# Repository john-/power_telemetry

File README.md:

Device that converts 12v to 5v, measures power/other things, and controls 4-wire fans.

# DESIGN NOTES

The 3rd 5V converter powers ICs and is a backup

**Power Sensing**

_Calibration_

V bus max   = 16V
V shunt max = 320㎷ (PGA = ÷8)
R shunt     = 0.1Ω

I max possible = V shunt max ÷ R shunt = 3.2A

I max expected = 3A (this needs to be revisited with better understanding of what it represents)

_Serial Bus Address_

Ground A0 and A1 to get adress of 1000000.

I²C bus pull-up resistors of 4.7KΩ was not calculated.  It was from arbitrary site.   The INA219 datasheet references 3.3KΩ.

_Optional Filter_

As filtering may not be needed initial implementation will be 0Ω resistors (R6/7) and capacitor (C3) unpopulated.

_Bypass Capacitors_

Values are taken from datasheet.  Ceramic type chosen from arbitrary page.

Design mistakes:

- I did not include any temp sensors! Now when I read the data sheet for the ADT7470 it makes it clear it is can't do standalone temperature measuring. I previously assumed it had one built-in temperature sensor. Anyway, I will use manual control of the ADT7470 based on temperature of SBCs (there will be 2 Odroid C2s in the case). I may add an external temperature sensor for the temperature sensor. Previously I have used 1 wire sensor. I need to confirm I can use 1 wire and I2C at same time on C2.
- The circuit puts out 5V I2C and the C2 max input voltage 3.3V. I happen to have a level shifter to get things working. I should have had the circuit output 3.3V I2C.
- I am pretty sure I should have included GND with the SDA/SCL lines. Since I had to use the level shifter I wound up pulling in 5V/GND from elsewhere in the circuit.

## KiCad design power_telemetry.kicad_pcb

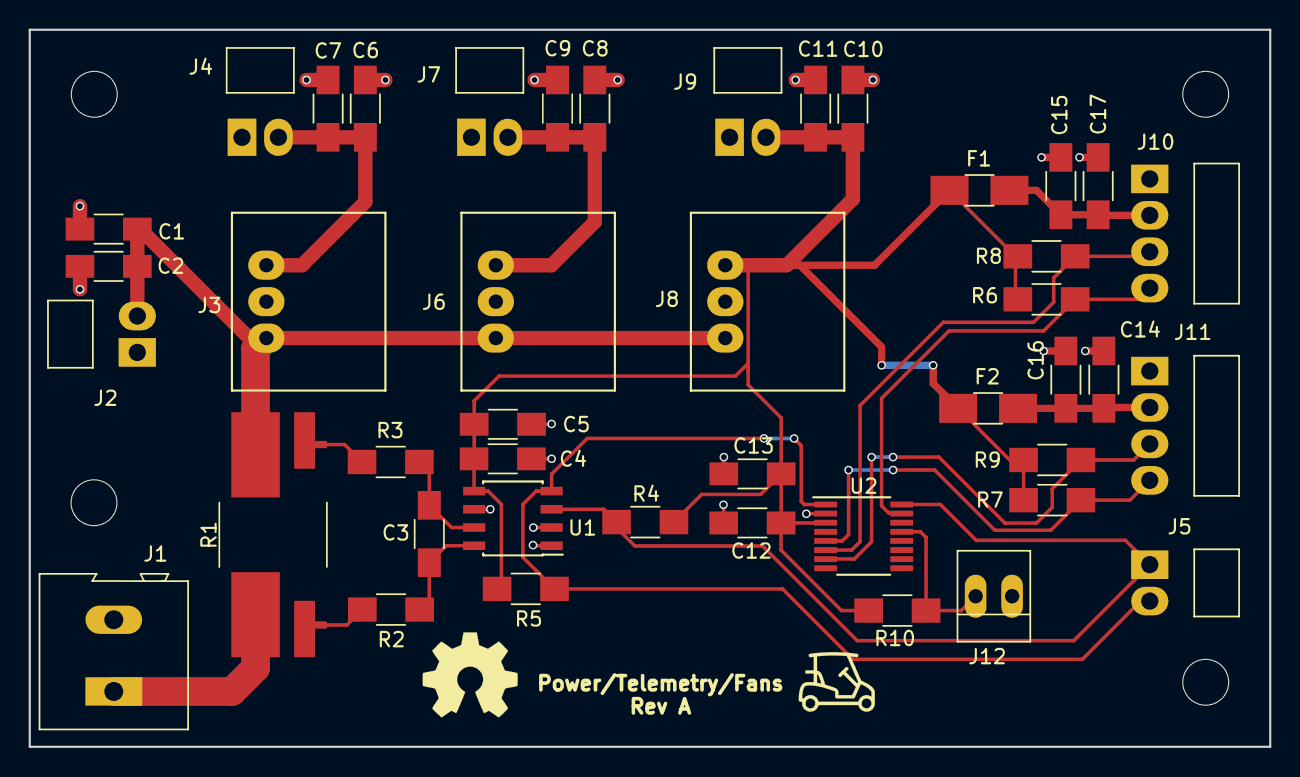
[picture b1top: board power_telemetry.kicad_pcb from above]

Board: 2 copper layers, 86.5 x 50.0 mm, 43 parts (0 on the bottom side), 17 nets.

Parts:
C1, C4, C6, C8, C10, C13, C15, C16: 10uF; C_1206_HandSoldering
C2, C5, C7, C9, C11, C12, C14, C17: 0.1uF; C_1206_HandSoldering
C3: C; C_1206_HandSoldering
F1, F2: 0.5A PTC; Fuse_SMD1206_HandSoldering
J1: Screw_Terminal_1x02; TER-202
J2, J4, J5, J7, J9: CONN_01X02; Molex_KK-171857-02x2.54mm_Right
J3, J6, J8: CONN_01X03; DCDC-Conv_Murata_OKI-78SR-E
J10, J11: CONN_01X04; Molex_KK-171857-04x2.54mm_Right
J12: GS2; PINHEAD1-2
R1: 100 mOhms; R_4527_Kelvin2_HandSoldering
R2, R3: 0k; R_1206_HandSoldering
R4, R5: 4.7k; R_1206_HandSoldering
R6, R7, R8, R9, R10: 10k; R_1206_HandSoldering
U1: TI_INA219_SOIC; SOIC-8_3.9x4.9mm_Pitch1.27mm
U2: AD_ADT7470_QSOP; QSOP-16_3.9x4.9mm_Pitch0.635mm

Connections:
+12V: C1.2, C2.2, J2.2, J3.1, J6.1, J8.1, R1.2, R3.1
/SCL: J5.2, R5.2, U1.4, U2.1
/SDA: J5.1, R4.2, U1.3, U2.16
/VCCA: C8.2, C9.1, J6.3, J7.2
/VCCB: C6.2, C7.2, J3.3, J4.2
GND: C1.1, C2.1, C4.2, C5.2, C6.1, C7.1, C8.1, C9.2, C10.1, C11.2, C12.2, C13.2, C14.2, C15.2, C16.2, C17.2, J1.2, J2.1, J3.2, J4.1, J6.2, J7.1, J8.2, J9.1, J10.1, J11.1, J12.1, U1.1, U1.2, U1.6, U2.2
unnamed: C3.1, R2.2, U1.8
unnamed: C3.2, R3.2, U1.7
unnamed: C14.1, C16.1, F2.2, J11.2
unnamed: C15.1, C17.1, F1.2, J10.2
unnamed: J1.1, R1.1, R2.1
unnamed: J10.3, R8.1, U2.6
unnamed: J10.4, R6.2, U2.15
unnamed: J11.3, R9.1, U2.7
unnamed: J11.4, R7.2, U2.5
unnamed: J12.2, R10.2, U2.13
VCC: C4.1, C5.1, C10.2, C11.1, C12.1, C13.1, F1.1, F2.1, J8.3, J9.2, R4.1, R5.1, R6.1, R7.1, R8.2, R9.2, R10.1, U1.5, U2.3

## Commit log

2017-10-15 early stages
2017-10-15 add a render of schematic
2017-10-15 updated .gitignore
2017-10-17 more pcb latyout
2017-10-17 add pcb render
2018-01-27 some changes
2018-02-04 added datasheets directory and started adding design notes to the readme
2018-02-27 using 5v fan, added graphics
2018-03-03 switched power connectors
2018-09-15 define some parts and switch to 4 pad shunt resistor
2018-09-16 re-annoted all items and starting routing from scratch again
2018-09-20 progress on pcb layout
2018-09-22 pcb now has all connections made
2018-09-22 fixed order of power supplies
2018-10-06 now using correctly sized shunt resistor
2018-10-06 fixed tracks off sense resistor
2018-10-06 new part for 10uF bypass caps
2018-10-12 create 4 terminal sense resistor pad layout
2018-10-13 now using 4 pad shunt resistor
2018-10-13 changed sense resistor to 4527
2018-10-13 fully switched to another sense resistor
2018-10-13 updated readme mostly
2018-11-02 documentation updates
2018-11-02 added current issues to documentation
